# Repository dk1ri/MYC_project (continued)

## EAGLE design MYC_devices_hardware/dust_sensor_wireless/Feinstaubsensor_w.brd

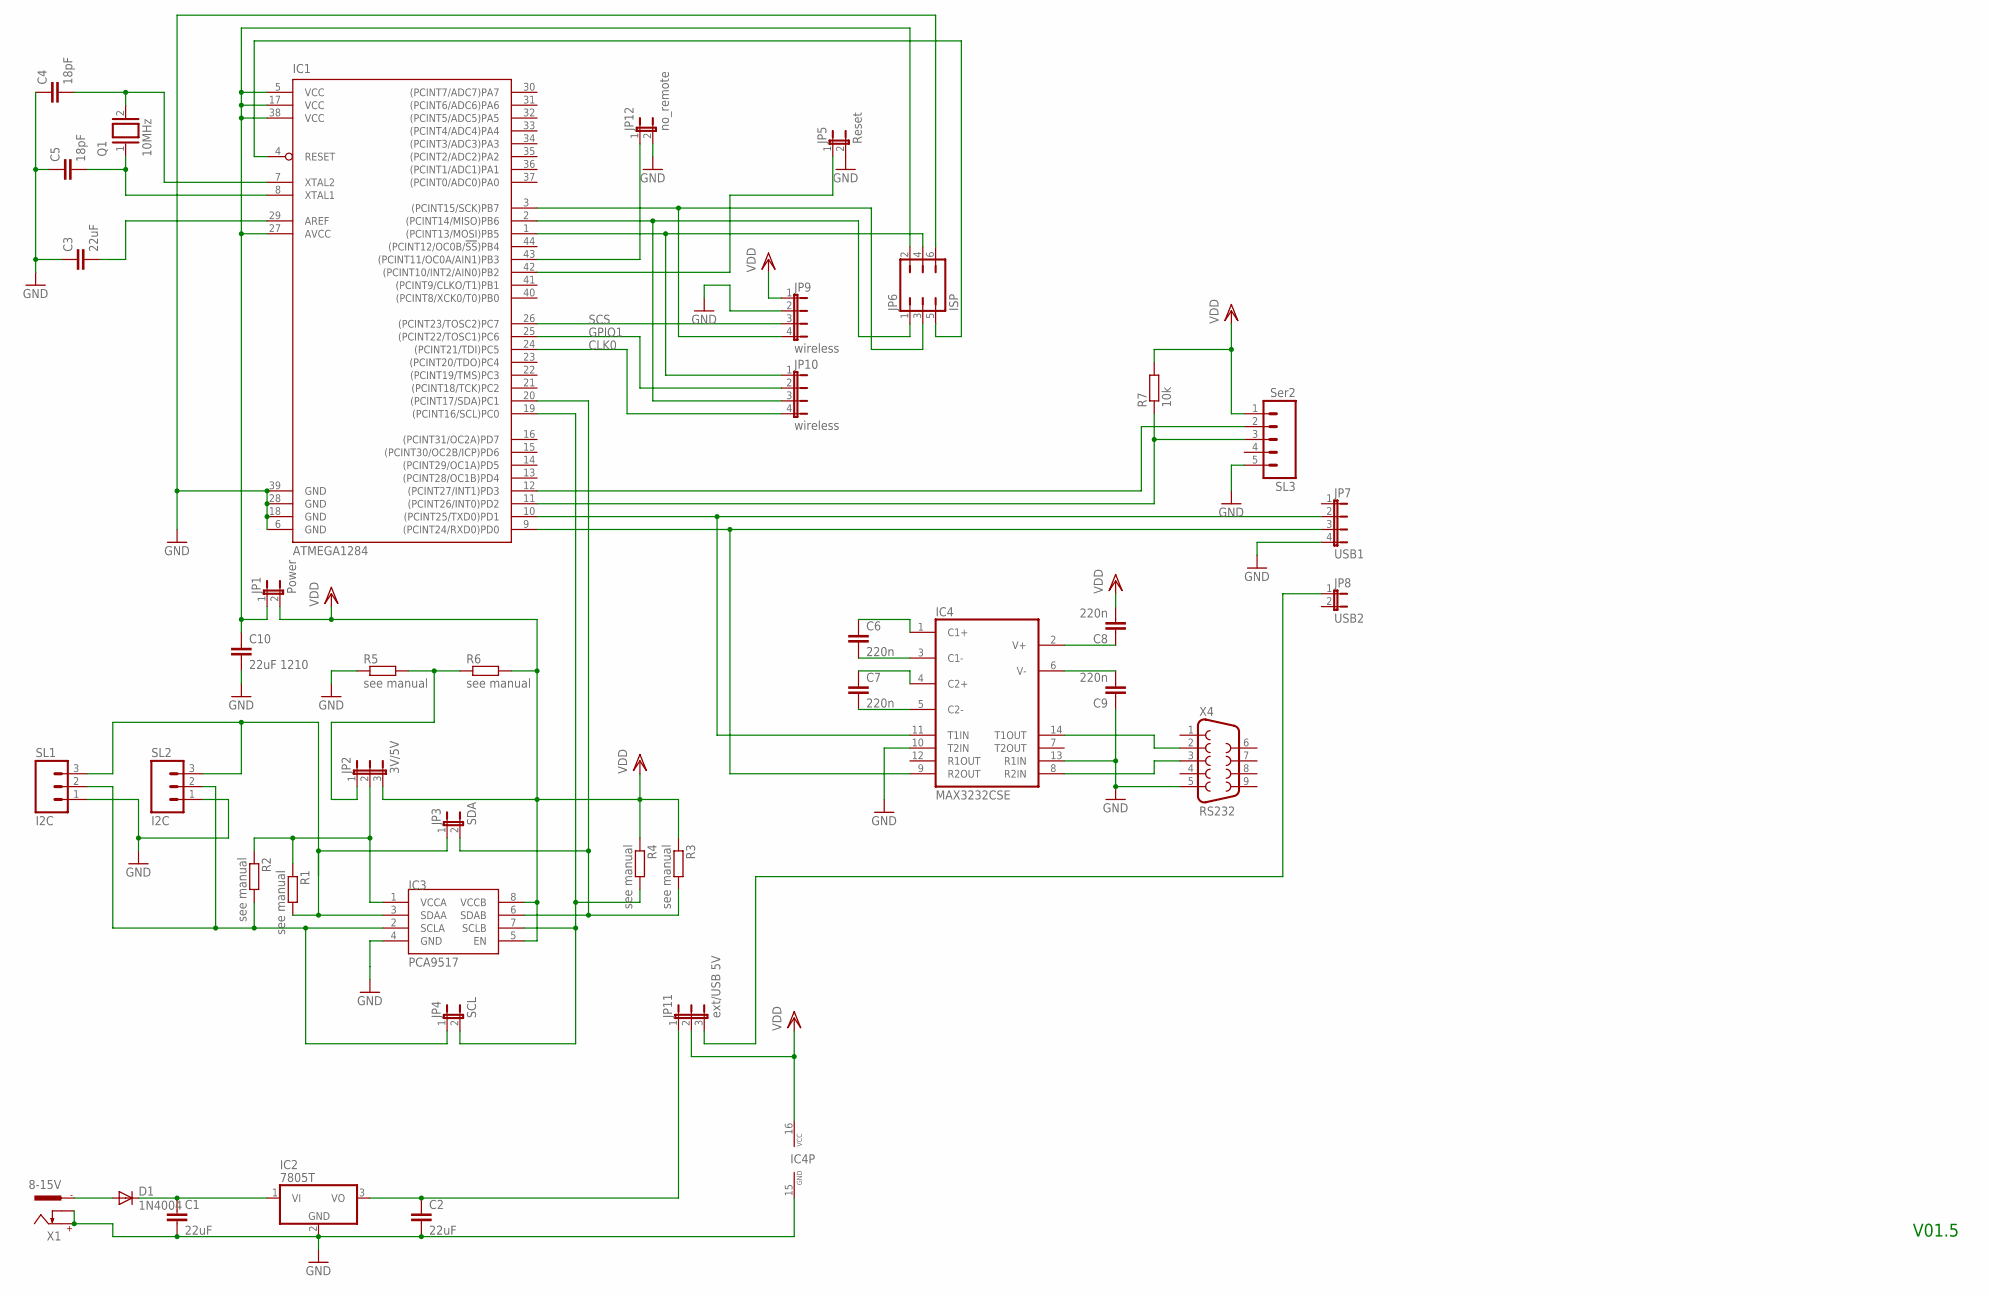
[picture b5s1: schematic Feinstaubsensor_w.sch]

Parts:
C1, C2, C3: 22uF; C1206
C4, C5: 18pF; C025-025X050
C6, C7, C8, C9: 220n; C1206
C10: 22uF 1210; C1206
D1: 1N4004; DO41-10
IC1: ATMEGA1284; TQFP44
IC2: 7805T; TO220H
IC3: PCA9517; SO-08
IC4: MAX3232CSE; SO16
JP1: Power; JP1
JP2: 3V/5V; JP2
JP3: SDA; JP1
JP4: SCL; JP1
JP5: Reset; JP1
JP6: ISP; JP3Q
JP7: USB1; JP4
JP8: USB2; JP1
JP9, JP10: wireless; JP4
JP11: ext/USB 5V; JP2
JP12: no_remote; JP1
Q1: 10MHz; QS
R1, R2, R3, R4, R5, R6: see manual; R1206
R7: 10k; R1206
SL1, SL2: I2C; 03P
SL3: Ser2; 05P
X1: 8-15V; 737992-5
X4: RS232; F09H

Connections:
C13: C6.1, IC4.1 (C1+)
CLK0: IC1.24 ((PCINT21/TDI)PC5), JP10.4
GND: C1.2, C2.2, C3.1, C4.1, C5.1, C9.1, C10.2, IC1.6 (GND), IC1.18 (GND), IC1.28 (GND), IC1.39 (GND), IC2.2 (GND), IC3.4 (GND), IC4.10 (T2IN), IC4.13 (R1IN), IC4.15 (GND), JP5.2, JP6.6, JP7.4, JP9.2, JP12.2, R5.1, SL1.1, SL2.1, SL3.5, X1.+, X1.K, X4.5
GPIO1: IC1.25 ((PCINT22/TOSC1)PC6), JP10.2
unnamed: IC1.9 ((PCINT24/RXD0)PD0), IC4.9 (R2OUT), JP7.3
unnamed: C7.2, IC4.5 (C2-)
unnamed: JP2.1, R5.2, R6.1
unnamed: IC1.20 ((PCINT17/SDA)PC1), IC3.6 (SDAB), JP3.2, R3.2
unnamed: C10.1, IC1.5 (VCC), IC1.17 (VCC), IC1.27 (AVCC), IC1.38 (VCC), JP1.1, JP6.2
unnamed: C4.2, IC1.7 (XTAL2), Q1.2
unnamed: IC1.1 ((PCINT13/MOSI)PB5), JP6.4, JP10.1
unnamed: IC4.14 (T1OUT), X4.2
unnamed: IC1.12 ((PCINT27/INT1)PD3), SL3.2
unnamed: IC1.10 ((PCINT25/TXD0)PD1), IC4.11 (T1IN), JP7.2
unnamed: C7.1, IC4.4 (C2+)
unnamed: C6.2, IC4.3 (C1-)
unnamed: IC1.42 ((PCINT10/INT2/AIN0)PB2), JP5.1
unnamed: C8.1, IC4.2 (V+)
unnamed: C9.2, IC4.6 (V-)
unnamed: IC1.4 (RESET), JP6.5
unnamed: IC1.11 ((PCINT26/INT0)PD2), R7.1, SL3.3
unnamed: IC1.43 ((PCINT11/OC0A/AIN1)PB3), JP12.1
unnamed: C5.2, IC1.8 (XTAL1), Q1.1
unnamed: IC1.19 ((PCINT16/SCL)PC0), IC3.7 (SCLB), JP4.2, R4.2
unnamed: IC3.3 (SDAA), JP3.1, R1.2, SL1.3, SL2.3
unnamed: C3.2, IC1.29 (AREF)
unnamed: IC3.2 (SCLA), JP4.1, R2.2, SL1.2, SL2.2
unnamed: IC1.3 ((PCINT15/SCK)PB7), JP6.3, JP9.4
unnamed: D1.A, X1.-1
unnamed: IC1.2 ((PCINT14/MISO)PB6), JP6.1, JP10.3
unnamed: C2.1, IC2.3 (VO), JP11.1
unnamed: IC3.1 (VCCA), JP2.2, R1.1, R2.1
unnamed: C1.1, D1.C, IC2.1 (VI)
unnamed: JP8.1, JP11.3
unnamed: IC4.8 (R2IN), X4.3
SCS: IC1.26 ((PCINT23/TOSC2)PC7), JP9.3
VDD: C8.2, IC3.5 (EN), IC3.8 (VCCB), IC4.16 (VCC), JP1.2, JP2.3, JP9.1, JP11.2, R3.1, R4.1, R6.2, R7.2, SL3.1

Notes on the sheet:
V01.5

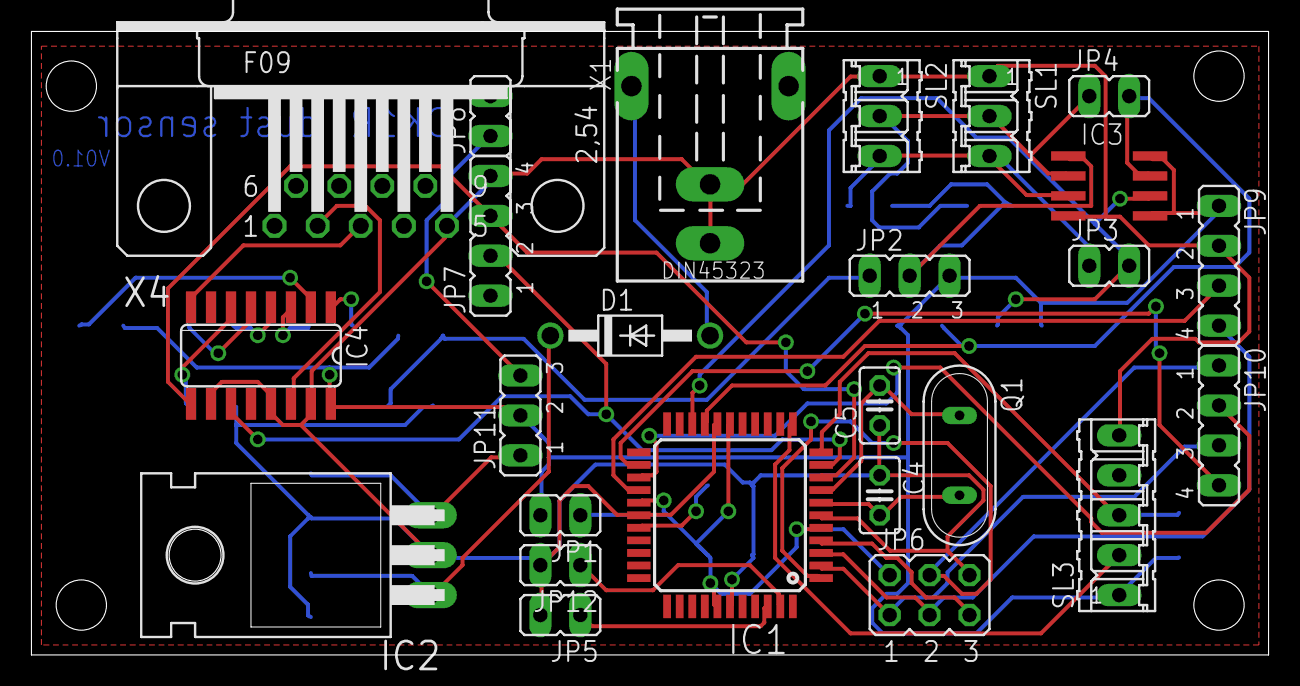
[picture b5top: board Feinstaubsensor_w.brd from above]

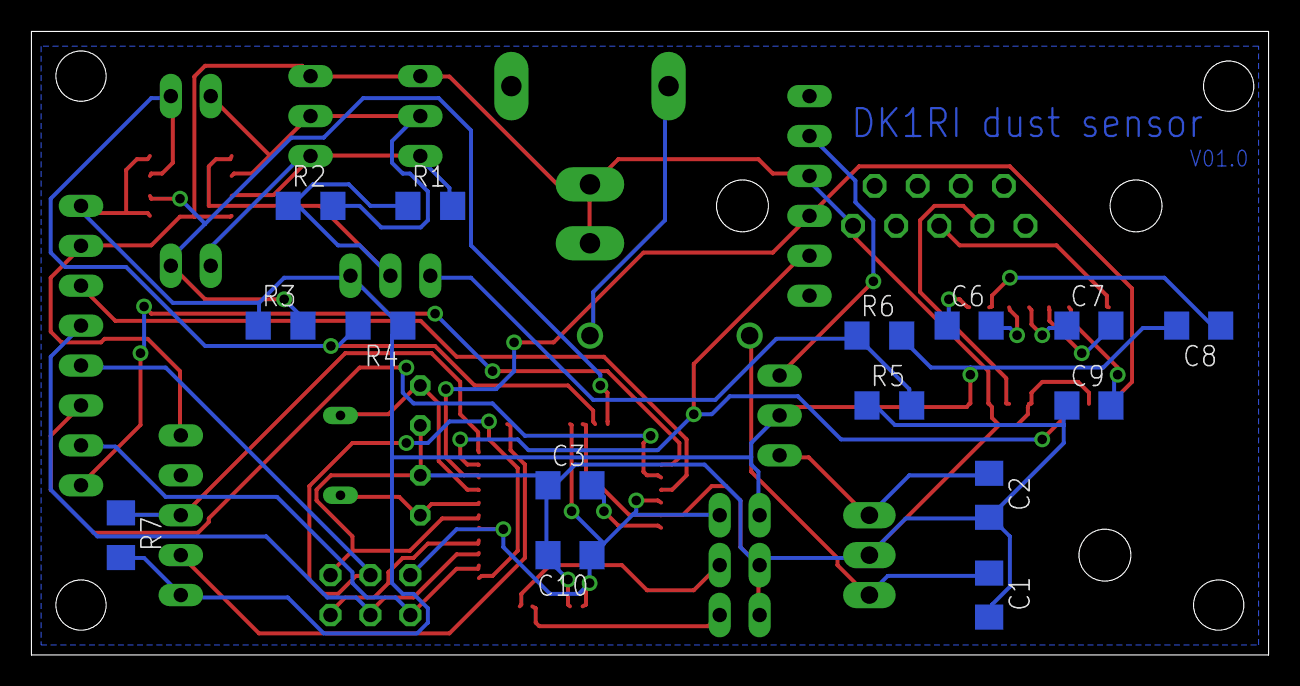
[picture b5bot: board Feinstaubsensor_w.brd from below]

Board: 2 copper layers, 78.7 x 39.7 mm, 40 parts (15 on the bottom side), 37 nets.

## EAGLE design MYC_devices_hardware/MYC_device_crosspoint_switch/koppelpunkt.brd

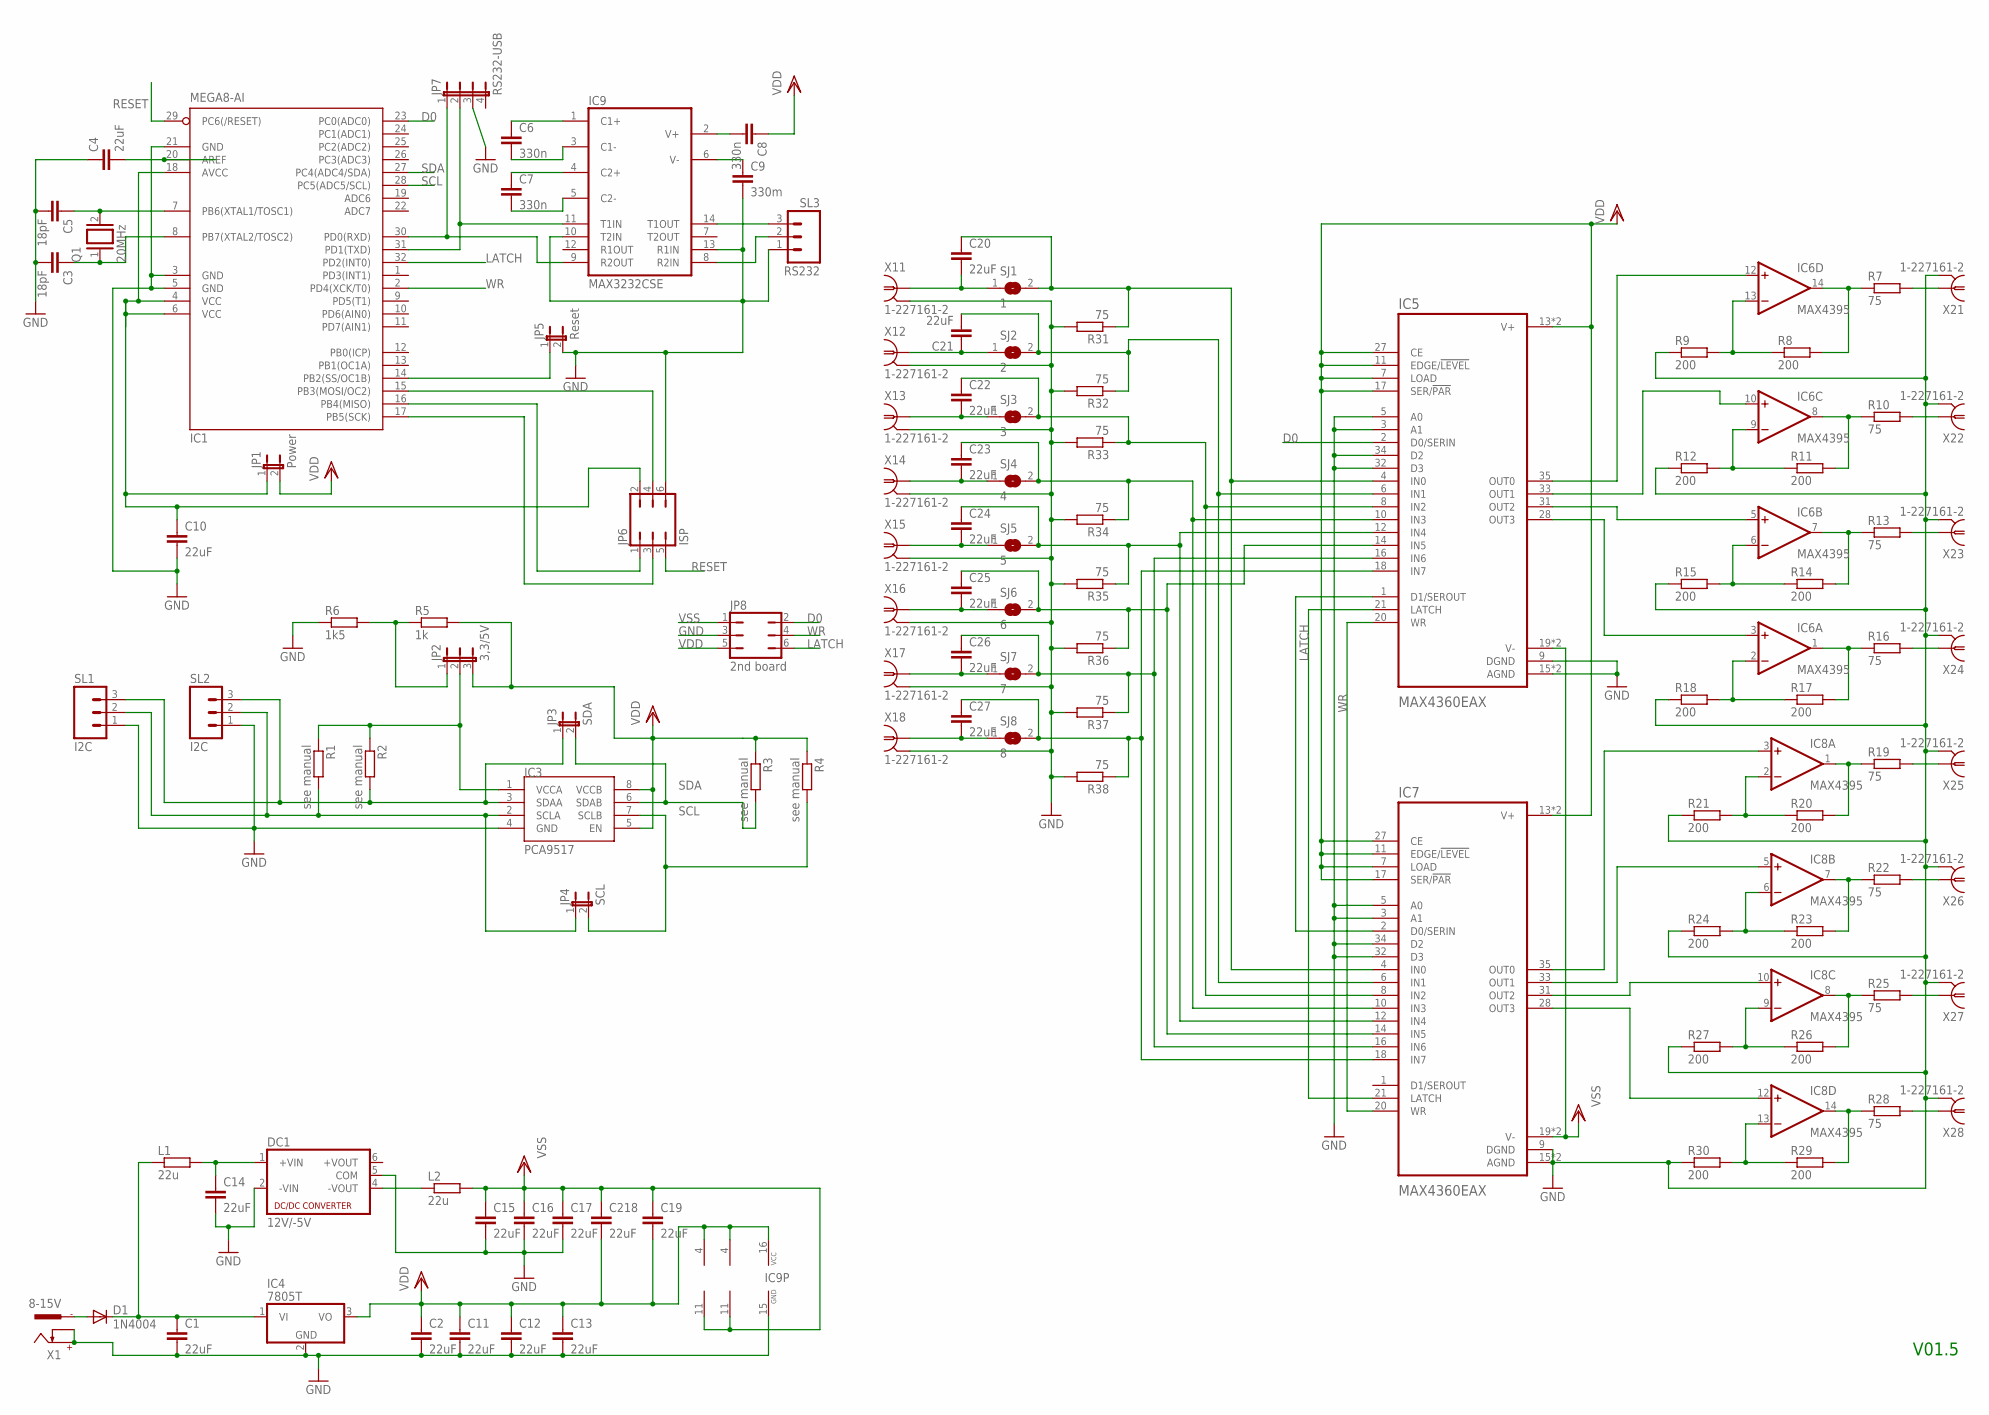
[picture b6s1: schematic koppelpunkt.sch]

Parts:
C1, C2, C4, C10, C11, C12, C13, C14, C15, C16, C17, C19, C20, C21, C22, C23, C24, C25, C26, C27, C218: 22uF; C1206
C3, C5: 18pF; C025-025X050
C6, C7, C8: 330n; C1206
C9: 330m; C1206
D1: 1N4004; DO41-10
DC1: 12V/-5V; NMA
IC1: MEGA8-AI; TQFP32-08
IC3: PCA9517; SO-08
IC4: 7805T; TO220H
IC5, IC7: MAX4360EAX; SOP80P1030X264-36N
IC6, IC8: MAX4395; SO14
IC9: MAX3232CSE; SO16
JP1: Power; JP1
JP2: 3,3/5V; JP2
JP3: SDA; JP1
JP4: SCL; JP1
JP5: Reset; JP1
JP6: ISP; JP3Q
JP7: RS232-USB; JP4
JP8: 2nd board; JP3Q
L1, L2: 22u; R6332
Q1: 20MHz; QS
R1, R2, R3, R4: see manual; R1206
R5: 1k; R1206
R6: 1k5; R1206
R7, R10, R13, R16, R19, R22, R25, R28, R31, R32, R33, R34, R35, R36, R37, R38: 75; R1206
R8, R11, R12, R14, R15, R17, R18, R20, R21, R23, R24, R26, R27, R29, R30: 200; R1206
R9: 200; M1206
SJ1: 1; SJ
SJ2: 2; SJ
SJ3: 3; SJ
SJ4: 4; SJ
SJ5: 5; SJ
SJ6: 6; SJ
SJ7: 7; SJ
SJ8: 8; SJ
SL1, SL2: I2C; 03P
SL3: RS232; 03P
X1: 8-15V; 737992-5
X11, X12, X13, X14, X15, X16, X17, X18, X21, X22, X23, X24, X25, X26, X27, X28: 1-227161-2; AMP_227161

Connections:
D0: IC1.23 (PC0(ADC0)), IC5.2 (D0/SERIN), JP8.2
GND: C1.2, C2.2, C3.2, C4.1, C5.2, C9.2, C10.2, C11.2, C12.2, C13.2, C14.2, C15.2, C16.2, C17.2, DC1.2 (-VIN), DC1.5 (COM), IC1.3 (GND), IC1.5 (GND), IC1.21 (GND), IC3.4 (GND), IC4.2 (GND), IC5.3 (A1), IC5.5 (A0), IC5.9 (DGND), IC5.15 (AGND), IC5.29 (AGND), IC5.32 (D3), IC5.34 (D2), IC7.3 (A1), IC7.5 (A0), IC7.9 (DGND), IC7.15 (AGND), IC7.29 (AGND), IC7.32 (D3), IC7.34 (D2), IC9.10 (T2IN), IC9.13 (R1IN), IC9.15 (GND), JP5.2, JP6.6, JP7.3, JP8.3, R6.1, R9.1, R12.1, R15.1, R18.1, R21.1, R24.1, R27.1, R30.1, R31.2, R32.2, R33.2, R34.2, R35.2, R36.2, R37.2, R38.2, SL1.1, SL2.1, SL3.1, X1.+, X1.K, X11.2, X12.2, X13.2, X14.2, X15.2, X16.2, X17.2, X18.2, X21.2, X22.2, X23.2, X24.2, X25.2, X26.2, X27.2, X28.2
LATCH: IC1.32 (PD2(INT0)), IC5.21 (LATCH), IC7.21 (LATCH), JP8.6
unnamed: C23.1, IC5.10 (IN3), IC7.10 (IN3), R34.1, SJ4.2
unnamed: C5.1, IC1.7 (PB6(XTAL1/TOSC1)), Q1.2
unnamed: C3.1, IC1.8 (PB7(XTAL2/TOSC2)), Q1.1
unnamed: C4.2, IC1.20 (AREF)
unnamed: IC3.3 (SDAA), JP3.1, R2.2, SL1.3, SL2.3
unnamed: IC1.16 (PB4(MISO)), JP6.1
unnamed: D1.A, X1.-1
unnamed: C10.1, IC1.4 (VCC), IC1.6 (VCC), IC1.18 (AVCC), JP1.1, JP6.2
unnamed: IC1.17 (PB5(SCK)), JP6.3
unnamed: IC1.14 (PB2(SS/OC1B)), JP5.1
unnamed: IC1.15 (PB3(MOSI/OC2)), JP6.4
unnamed: C7.2, IC9.5 (C2-)
unnamed: IC3.1 (VCCA), JP2.2, R1.1, R2.1
unnamed: IC3.2 (SCLA), JP4.1, R1.2, SL1.2, SL2.2
unnamed: IC9.14 (T1OUT), SL3.3
unnamed: C8.2, IC9.2 (V+)
unnamed: C22.1, IC5.8 (IN2), IC7.8 (IN2), R33.1, SJ3.2
unnamed: R7.2, X21.1
unnamed: IC6.14 (OUT), R7.1, R8.2
unnamed: IC9.8 (R2IN), SL3.2
unnamed: IC6.13 (-IN), R8.1, R9.2
unnamed: C7.1, IC9.4 (C2+)
unnamed: R10.2, X22.1
unnamed: JP2.1, R5.1, R6.2
unnamed: IC6.8 (OUT), R10.1, R11.2
unnamed: IC6.9 (-IN), R11.1, R12.2
unnamed: R13.2, X23.1
unnamed: C9.1, IC9.6 (V-)
unnamed: IC5.1 (D1/SEROUT), IC7.2 (D0/SERIN)
unnamed: IC6.7 (OUT), R13.1, R14.2
unnamed: IC6.6 (-IN), R14.1, R15.2
unnamed: C1.1, D1.C, IC4.1 (VI), L1.1
unnamed: IC1.30 (PD0(RXD)), IC9.9 (R2OUT), JP7.1
unnamed: R22.2, X26.1
unnamed: IC8.7 (OUT), R22.1, R23.2
unnamed: IC8.6 (-IN), R23.1, R24.2
unnamed: IC6.1 (OUT), R16.1, R17.2
unnamed: R16.2, X24.1
unnamed: IC6.2 (-IN), R17.1, R18.2
unnamed: IC8.9 (-IN), R26.1, R27.2
unnamed: IC8.2 (-IN), R20.1, R21.2
unnamed: IC8.1 (OUT), R19.1, R20.2
unnamed: IC1.31 (PD1(TXD)), IC9.11 (T1IN), JP7.2
unnamed: R19.2, X25.1
unnamed: R25.2, X27.1
unnamed: IC8.8 (OUT), R25.1, R26.2
unnamed: C6.1, IC9.1 (C1+)
unnamed: R28.2, X28.1
unnamed: IC8.14 (OUT), R28.1, R29.2
unnamed: IC8.13 (-IN), R29.1, R30.2
unnamed: C6.2, IC9.3 (C1-)
unnamed: IC5.35 (OUT0), IC6.12 (+IN)
unnamed: IC5.33 (OUT1), IC6.10 (+IN)
unnamed: IC5.31 (OUT2), IC6.5 (+IN)
unnamed: IC5.28 (OUT3), IC6.3 (+IN)
unnamed: C14.1, DC1.1 (+VIN), L1.2
unnamed: IC7.35 (OUT0), IC8.3 (+IN)
unnamed: C20.2, SJ1.1, X11.1
unnamed: C26.1, IC5.16 (IN6), IC7.16 (IN6), R37.1, SJ7.2
unnamed: IC7.33 (OUT1), IC8.5 (+IN)
unnamed: IC7.31 (OUT2), IC8.10 (+IN)
unnamed: IC7.28 (OUT3), IC8.12 (+IN)
unnamed: C21.1, SJ2.1, X12.1
unnamed: C22.2, SJ3.1, X13.1
unnamed: C20.1, IC5.4 (IN0), IC7.4 (IN0), R31.1, SJ1.2
unnamed: C21.2, IC5.6 (IN1), IC7.6 (IN1), R32.1, SJ2.2
unnamed: C23.2, SJ4.1, X14.1
unnamed: C24.2, SJ5.1, X15.1
unnamed: C24.1, IC5.12 (IN4), IC7.12 (IN4), R35.1, SJ5.2
unnamed: C25.2, SJ6.1, X16.1
unnamed: C26.2, SJ7.1, X17.1
unnamed: C27.2, SJ8.1, X18.1
unnamed: C27.1, IC5.18 (IN7), IC7.18 (IN7), R38.1, SJ8.2
unnamed: DC1.4 (-VOUT), L2.1
unnamed: C25.1, IC5.14 (IN5), IC7.14 (IN5), R36.1, SJ6.2
RESET: IC1.29 (PC6(/RESET)), JP6.5
SCL: IC1.28 (PC5(ADC5/SCL)), IC3.7 (SCLB), JP4.2, R4.2
SDA: IC1.27 (PC4(ADC4/SDA)), IC3.6 (SDAB), JP3.2, R3.2
VDD: C2.1, C8.1, C11.1, C12.1, C13.1, C19.2, C218.2, IC3.5 (EN), IC3.8 (VCCB), IC4.3 (VO), IC5.7 (LOAD), IC5.11 (EDGE/!LEVEL), IC5.13 (V+), IC5.17 (SER/!PAR), IC5.27 (CE), IC5.36 (V+), IC6.4 (V+), IC7.7 (LOAD), IC7.11 (EDGE/!LEVEL), IC7.13 (V+), IC7.17 (SER/!PAR), IC7.27 (CE), IC7.36 (V+), IC8.4 (V+), IC9.16 (VCC), JP1.2, JP2.3, JP8.5, R3.1, R4.1, R5.2
VSS: C15.1, C16.1, C17.1, C19.1, C218.1, IC5.19 (V-), IC5.30 (V-), IC6.11 (V-), IC7.19 (V-), IC7.30 (V-), IC8.11 (V-), JP8.1, L2.2
WR: IC1.2 (PD4(XCK/T0)), IC5.20 (WR), IC7.20 (WR), JP8.4

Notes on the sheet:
V01.5

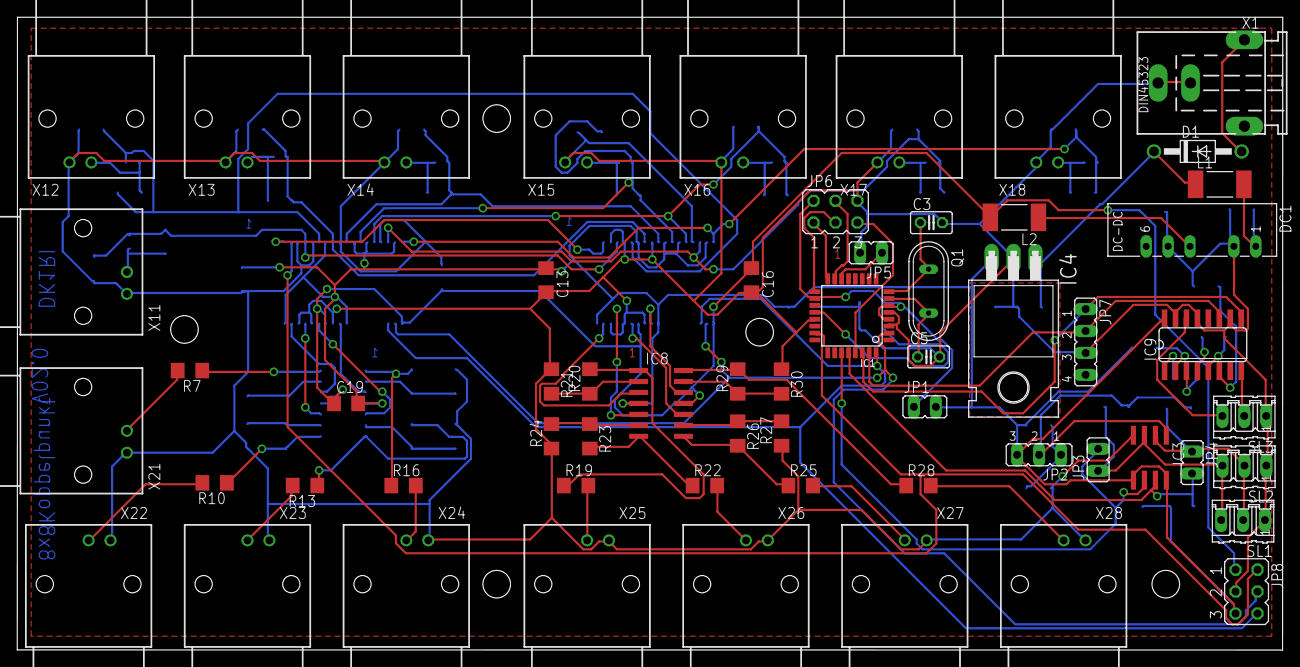
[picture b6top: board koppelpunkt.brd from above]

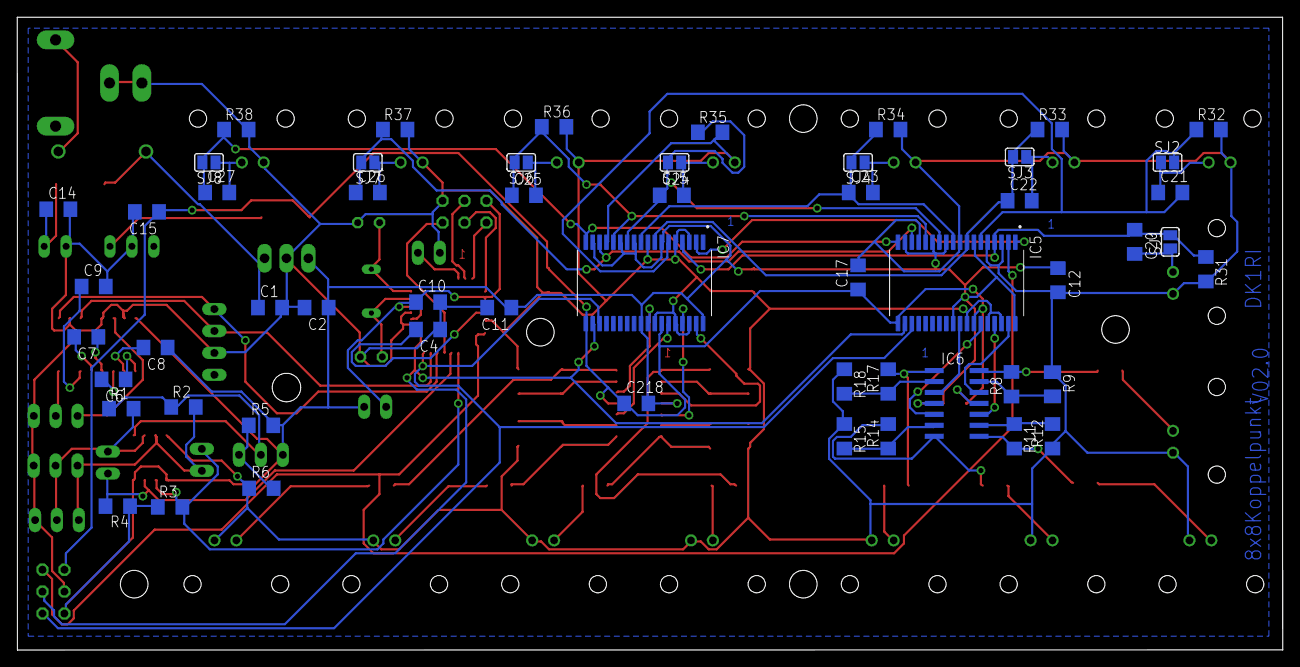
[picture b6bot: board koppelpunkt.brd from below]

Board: 3 copper layers, 146.7 x 73.4 mm, 114 parts (55 on the bottom side), 84 nets.

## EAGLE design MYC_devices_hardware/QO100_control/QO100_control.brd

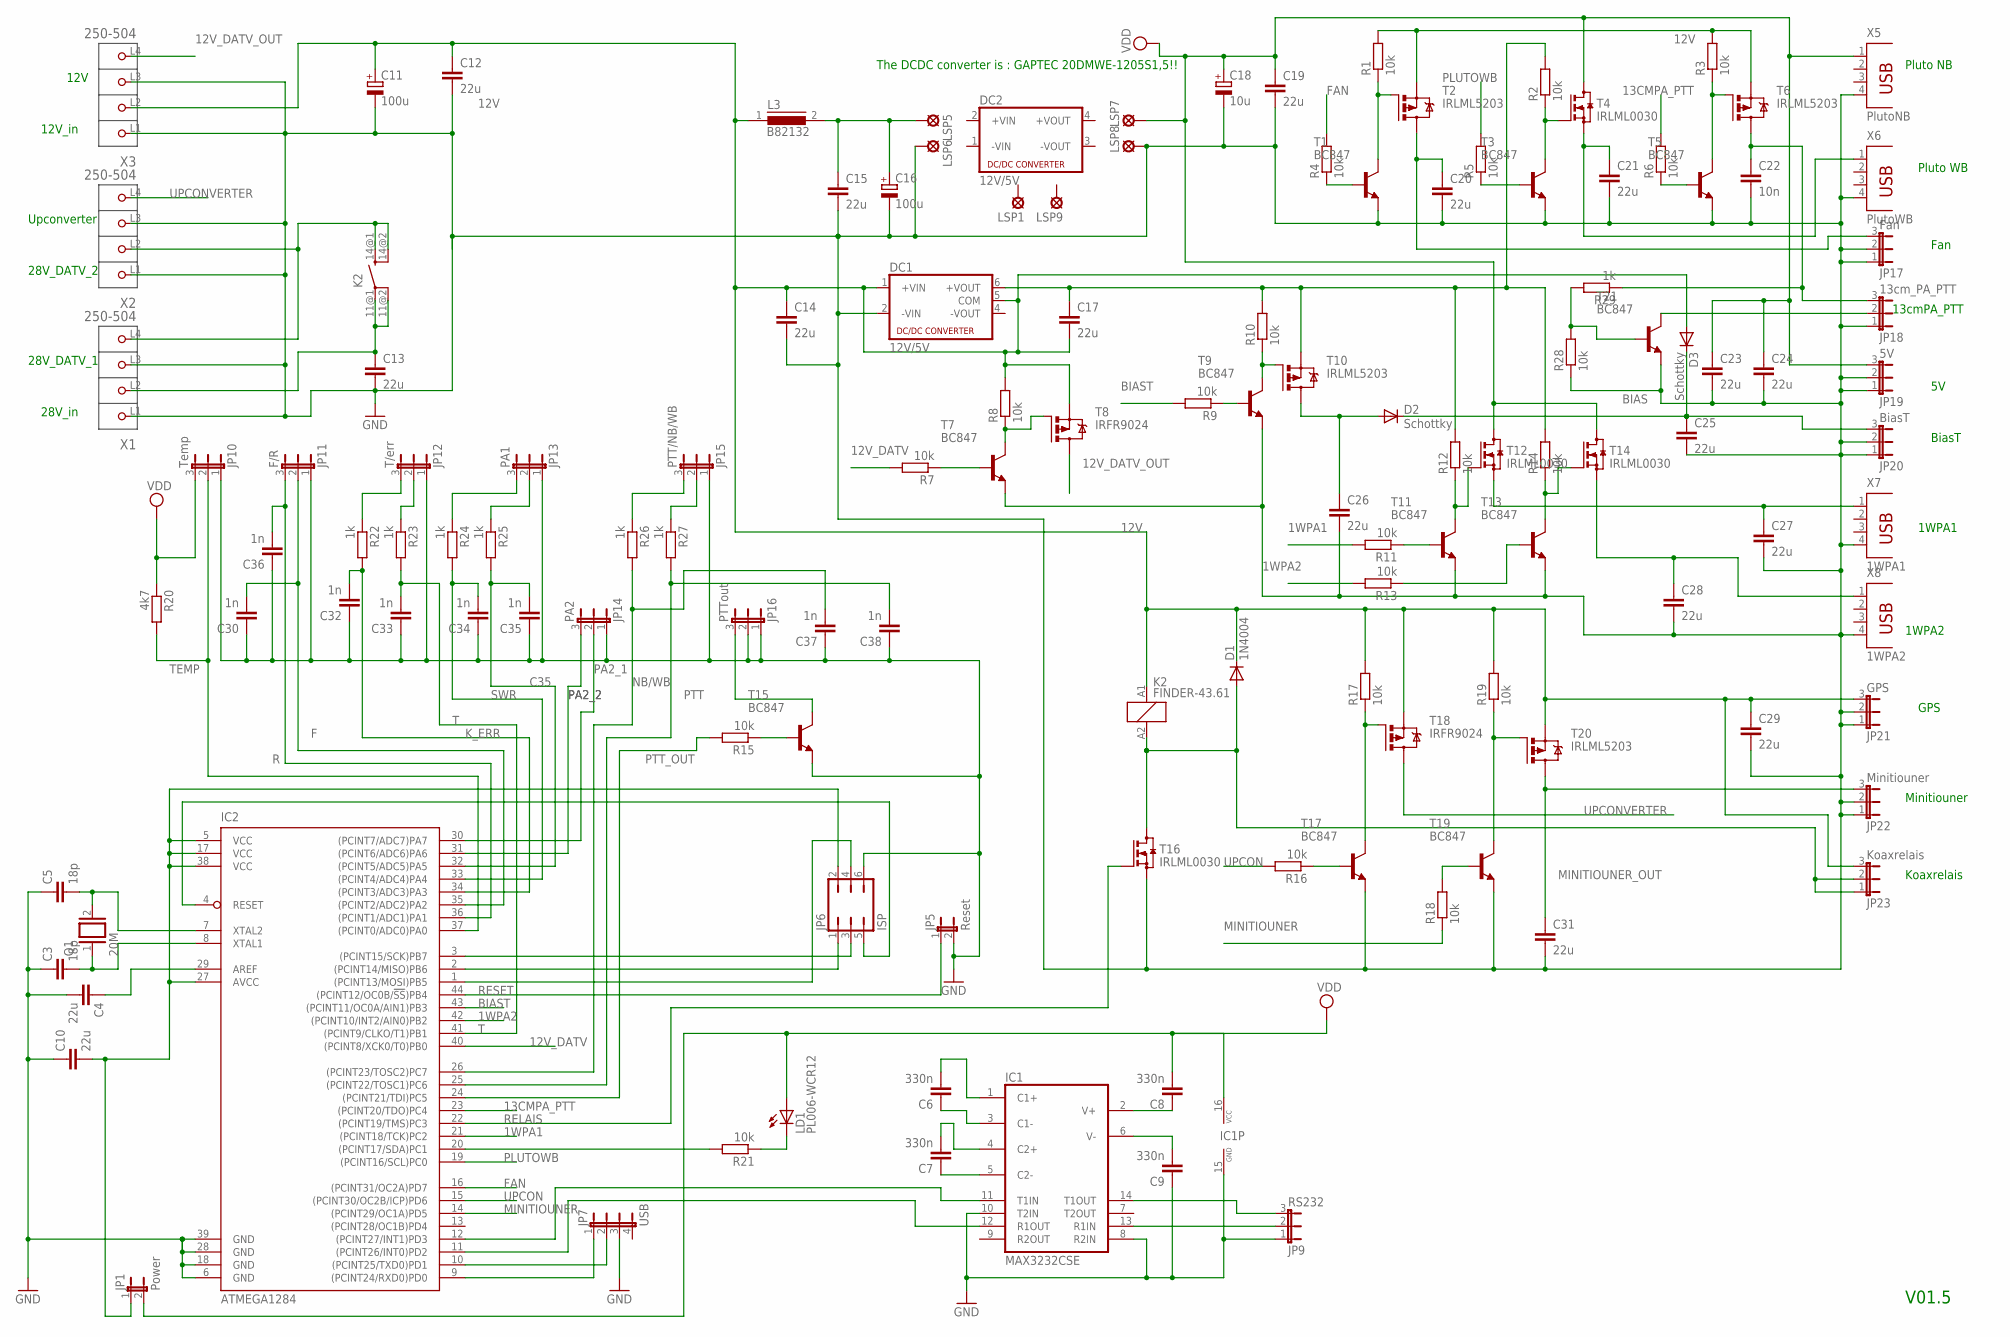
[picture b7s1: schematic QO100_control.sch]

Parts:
C3, C5: 18p; C025-025X050
C4, C10, C12, C13, C14, C15, C17, C19, C20, C21, C23, C24, C25, C26, C27, C28, C29, C31: 22u; C1206
C6, C7, C8, C9: 330n; C1206
C11, C16: 100u; E5-6
C18: 10u; E5-6
C22: 10n; C1206
C30, C32, C33, C34, C35, C36, C37, C38: 1n; C1206
D1: 1N4004; DO41-10
D2, D3: Schottky; DO41-10
DC1: 12V/5V; NMA
DC2: 12V/5V; NME
IC1: MAX3232CSE; SO16
IC2: ATMEGA1284; TQFP44
JP1: Power; JP1
JP5: Reset; JP1
JP6: ISP; JP3Q
JP7: USB; JP4
JP9: RS232; JP2
JP10: Temp; JP2
JP11: F/R; JP2
JP12: T/err; JP2
JP13: PA1; JP2
JP14: PA2; JP2
JP15: PTT/NB/WB; JP2
JP16: PTTout; JP2
JP17: Fan; JP2
JP18: 13cm_PA_PTT; JP2
JP19: 5V; JP2
JP20: BiasT; JP2
JP21: GPS; JP2
JP22: Minitiouner; JP2
JP23: Koaxrelais; JP2
K2: FINDER-43.61
L3: B82132; SUKW2-22
LD1: PL006-WCR12; SOT23
LSP1, LSP5, LSP6, LSP7, LSP8, LSP9: SE14
Q1: 20M; QS
R1, R2, R3, R4, R5, R6, R7, R8, R9, R10, R11, R12, R13, R14, R15, R16, R17, R18, R19, R21, R28: 10k; R1206
R20: 4k7; R1206
R22, R23, R24, R25, R26, R27, R29: 1k; R1206
T1, T3, T5, T7, T9, T11, T13, T15, T17, T19, T21: BC847; SOT23
T2, T6, T10, T20: IRLML5203; MICRO3
T4, T12, T14, T16: IRLML0030; SOT23
T8, T18: IRFR9024; D-PAK_TO252AA
X1, X2, X3: 250-504; P-250-504
X5: PlutoNB; PN87520
X6: PlutoWB; PN87520
X7: 1WPA1; PN87520
X8: 1WPA2; PN87520

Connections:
1WPA1: IC2.21 ((PCINT18/TCK)PC2), R11.2
1WPA2: IC2.42 ((PCINT10/INT2/AIN0)PB2), R13.2
12V: C11.+, C12.1, C14.1, C17.2, C29.1, D1.C, D3.A, DC1.1 (+VIN), DC1.5 (COM), JP21.3, JP23.3, K2.A1 (1), L3.1, R1.2, R3.2, R8.2, R17.2, R19.2, T2.2 (S), T6.2 (S), T8.3 (S), T18.3 (S), T20.2 (S), X3.L2 (P2)
12V_DATV: IC2.40 ((PCINT8/XCK0/T0)PB0), R7.2
12V_DATV_OUT: T8.4 (D), X3.L4 (P4)
13CMPA_PTT: IC2.23 ((PCINT20/TDO)PC4), R6.2
28V: K2.14@1 (SA), K2.14@2 (SB), X1.L4 (P4), X2.L2 (P2)
BIAS: C25.1, D2.C, D3.C, JP20.3
BIAST: IC2.43 ((PCINT11/OC0A/AIN1)PB3), R9.2
C35: C35.2, IC2.32 ((PCINT5/ADC5)PA5), R25.2
DFGJKN: C26.1, D2.A, T10.3 (D)
F: C30.2, IC2.35 ((PCINT2/ADC2)PA2), JP11.2
FAN: IC2.16 ((PCINT31/OC2A)PD7), R4.2
GND: C3.1, C4.2, C5.1, C9.1, C10.1, C11.-, C12.2, C13.2, C14.2, C15.2, C16.-, C18.-, C19.2, C20.2, C21.2, C22.2, C23.2, C24.2, C25.2, C26.2, C27.2, C28.2, C29.2, C30.1, C31.2, C32.1, C33.1, C34.1, C35.1, C36.1, C37.1, C38.1, DC1.2 (-VIN), IC1.8 (R2IN), IC1.10 (T2IN), IC1.15 (GND), IC2.6 (GND), IC2.18 (GND), IC2.28 (GND), IC2.39 (GND), JP5.2, JP6.6, JP7.3, JP9.1, JP10.1, JP11.1, JP12.1, JP13.1, JP14.1, JP15.1, JP16.1, JP16.2, JP17.1, JP17.2, JP18.1, JP19.1, JP19.2, JP20.1, JP20.2, JP21.1, JP21.2, JP22.1, JP22.2, LSP6.MP, LSP8.MP, R28.1, T1.2 (E), T3.2 (E), T5.2 (E), T7.2 (E), T9.2 (E), T11.2 (E), T13.2 (E), T15.2 (E), T16.2 (S), T17.2 (E), T19.2 (E), T21.2 (E), X1.L1 (P1), X1.L3 (P3), X2.L1 (P1), X2.L3 (P3), X3.L1 (P1), X3.L3 (P3), X5.4, X6.4, X7.4, X8.4
K_ERR: C32.2, IC2.34 ((PCINT3/ADC3)PA3), R22.2
MINITIOUNER: IC2.14 ((PCINT29/OC1A)PD5), R18.1
MINITIOUNER_OUT: C31.1, JP22.3, T20.3 (D)
unnamed: IC2.20 ((PCINT17/SDA)PC1), R21.2
unnamed: C22.1, JP18.3, R29.1, T6.3 (D)
unnamed: C28.1, T14.2 (S), X8.1
unnamed: IC2.3 ((PCINT15/SCK)PB7), JP6.3
unnamed: R17.1, T17.3 (C), T18.1 (G)
unnamed: C5.2, IC2.7 (XTAL2), Q1.2
unnamed: C15.1, C16.+, L3.2, LSP5.MP
unnamed: R8.1, T7.3 (C), T8.1 (G)
unnamed: LD1.3 (C), R21.1
unnamed: C3.2, IC2.8 (XTAL1), Q1.1
unnamed: R7.1, T7.1 (B)
unnamed: JP12.3, R22.1
unnamed: IC2.2 ((PCINT14/MISO)PB6), JP6.1
unnamed: C6.2, IC1.1 (C1+)
unnamed: IC2.1 ((PCINT13/MOSI)PB5), JP6.4
unnamed: IC2.4 (RESET), JP6.5
unnamed: IC2.9 ((PCINT24/RXD0)PD0), JP7.1
unnamed: IC2.10 ((PCINT25/TXD0)PD1), JP7.2
unnamed: IC1.12 (R1OUT), IC2.11 ((PCINT26/INT0)PD2)
unnamed: C4.1, IC2.29 (AREF)
unnamed: IC1.11 (T1IN), IC2.12 ((PCINT27/INT1)PD3)
unnamed: JP12.2, R23.1
unnamed: JP13.2, R25.1
unnamed: JP13.3, R24.1
unnamed: JP15.3, R26.1
unnamed: C27.1, T12.2 (S), X7.1
unnamed: JP15.2, R27.1
unnamed: D1.A, JP23.1, JP23.2, K2.A2 (2), T16.3 (D)
unnamed: C6.1, IC1.3 (C1-)
unnamed: C7.1, IC1.5 (C2-)
unnamed: C7.2, IC1.4 (C2+)
unnamed: JP18.2, T21.3 (C)
unnamed: IC1.14 (T1OUT), JP9.3
unnamed: C9.2, IC1.6 (V-)
unnamed: C8.1, IC1.2 (V+)
unnamed: IC1.13 (R1IN), JP9.2
unnamed: R28.2, R29.2, T21.1 (B)
unnamed: R3.1, T5.3 (C), T6.1 (G)
unnamed: JP16.3, T15.3 (C)
unnamed: C21.1, T4.2 (S), X6.1
unnamed: R15.1, T15.1 (B)
unnamed: R19.1, T19.3 (C), T20.1 (G)
unnamed: R10.1, T9.3 (C), T10.1 (G)
unnamed: R6.1, T5.1 (B)
unnamed: C20.1, JP17.3, T2.3 (D)
unnamed: R2.1, T3.3 (C), T4.1 (G)
unnamed: R12.1, T11.3 (C), T12.1 (G)
unnamed: R1.1, T1.3 (C), T2.1 (G)
unnamed: C17.1, DC1.6 (+VOUT), R2.2, R10.2, R12.2, R14.2, T10.2 (S)
unnamed: R14.1, T13.3 (C), T14.1 (G)
unnamed: R4.1, T1.1 (B)
unnamed: R5.1, T3.1 (B)
unnamed: R9.1, T9.1 (B)
unnamed: R11.1, T11.1 (B)
unnamed: R13.1, T13.1 (B)
unnamed: R16.1, T17.1 (B)
unnamed: C13.1, K2.11@1 (PA), K2.11@2 (PB), X1.L2 (P2)
unnamed: R18.2, T19.1 (B)
NB/WB: C37.2, IC2.26 ((PCINT23/TOSC2)PC7), R26.2
PA2_1: IC2.30 ((PCINT7/ADC7)PA7), JP14.2
PA2_2: IC2.31 ((PCINT6/ADC6)PA6), JP14.3
PLUTOWB: IC2.19 ((PCINT16/SCL)PC0), R5.2
PTT: C38.2, IC2.25 ((PCINT22/TOSC1)PC6), R27.2
PTT_OUT: IC2.24 ((PCINT21/TDI)PC5), R15.2
R: C36.2, IC2.36 ((PCINT1/ADC1)PA1), JP11.3
RELAIS: IC2.22 ((PCINT19/TMS)PC3), T16.1 (G)
RESET: IC2.44 ((PCINT12/OC0B/!SS!)PB4), JP5.1
SWR: C34.2, IC2.33 ((PCINT4/ADC4)PA4), R24.2
T: C33.2, IC2.41 ((PCINT9/CLKO/T1)PB1), R23.2
TEMP: IC2.37 ((PCINT0/ADC0)PA0), JP10.2, R20.2
UPCON: IC2.15 ((PCINT30/OC2B/ICP)PD6), R16.2
UPCONVERTER: T18.4 (D), X2.L4 (P4)
VCC: C10.2, IC2.5 (VCC), IC2.17 (VCC), IC2.27 (AVCC), IC2.38 (VCC), JP1.1, JP6.2
VDD: C8.2, C18.+, C19.1, C23.1, C24.1, IC1.16 (VCC), JP1.2, JP10.3, JP19.3, LD1.1 (A), LSP7.MP, R20.1, T4.3 (D), T12.3 (D), T14.3 (D), X5.1

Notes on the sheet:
V01.5
28V_in
BiasT
1WPA2
Koaxrelais
Upconverter
GPS
The DCDC converter is : GAPTEC 20DMWE-1205S1,5!!
Pluto NB
Pluto WB
Fan
13cmPA_PTT
12V_in
12V
28V_DATV_1
28V_DATV_2
1WPA1
Minitiouner

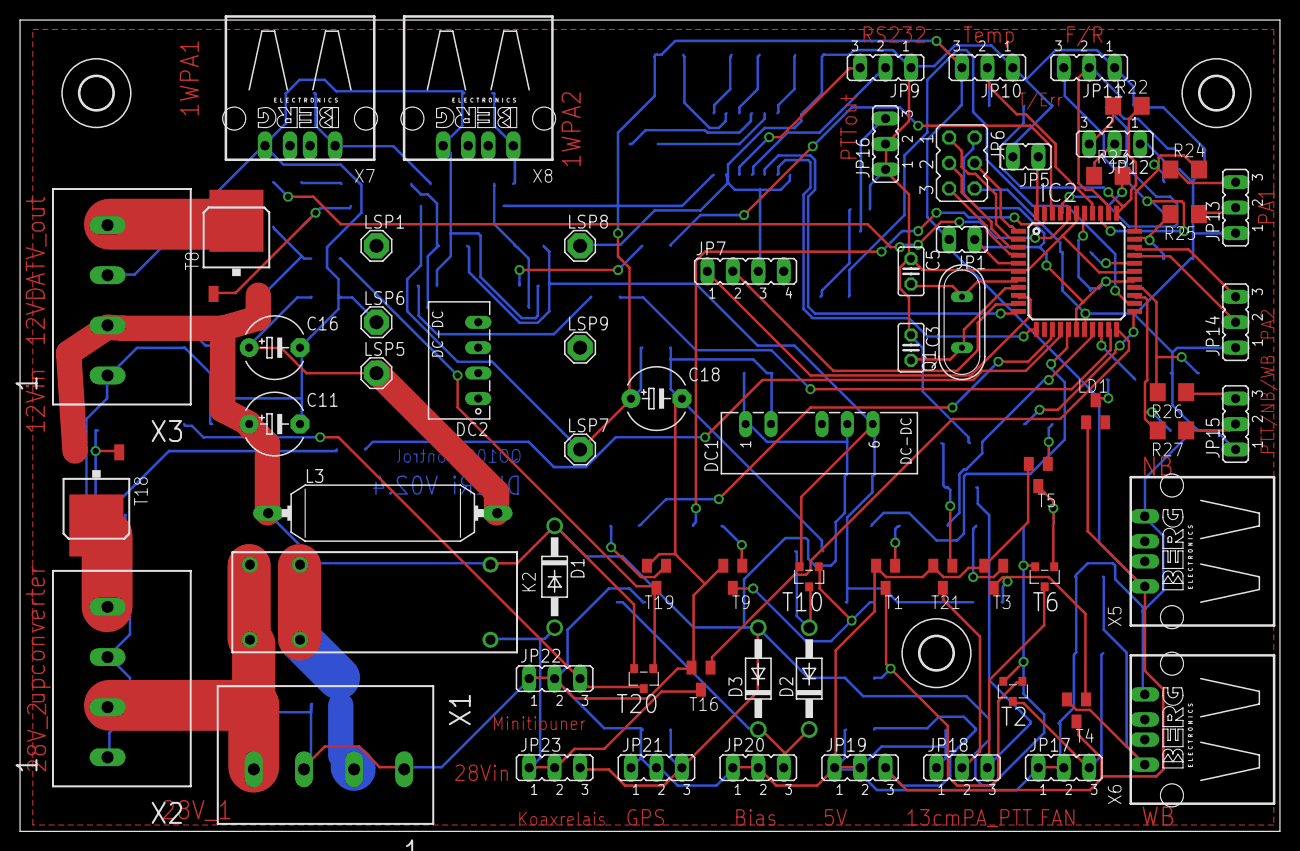
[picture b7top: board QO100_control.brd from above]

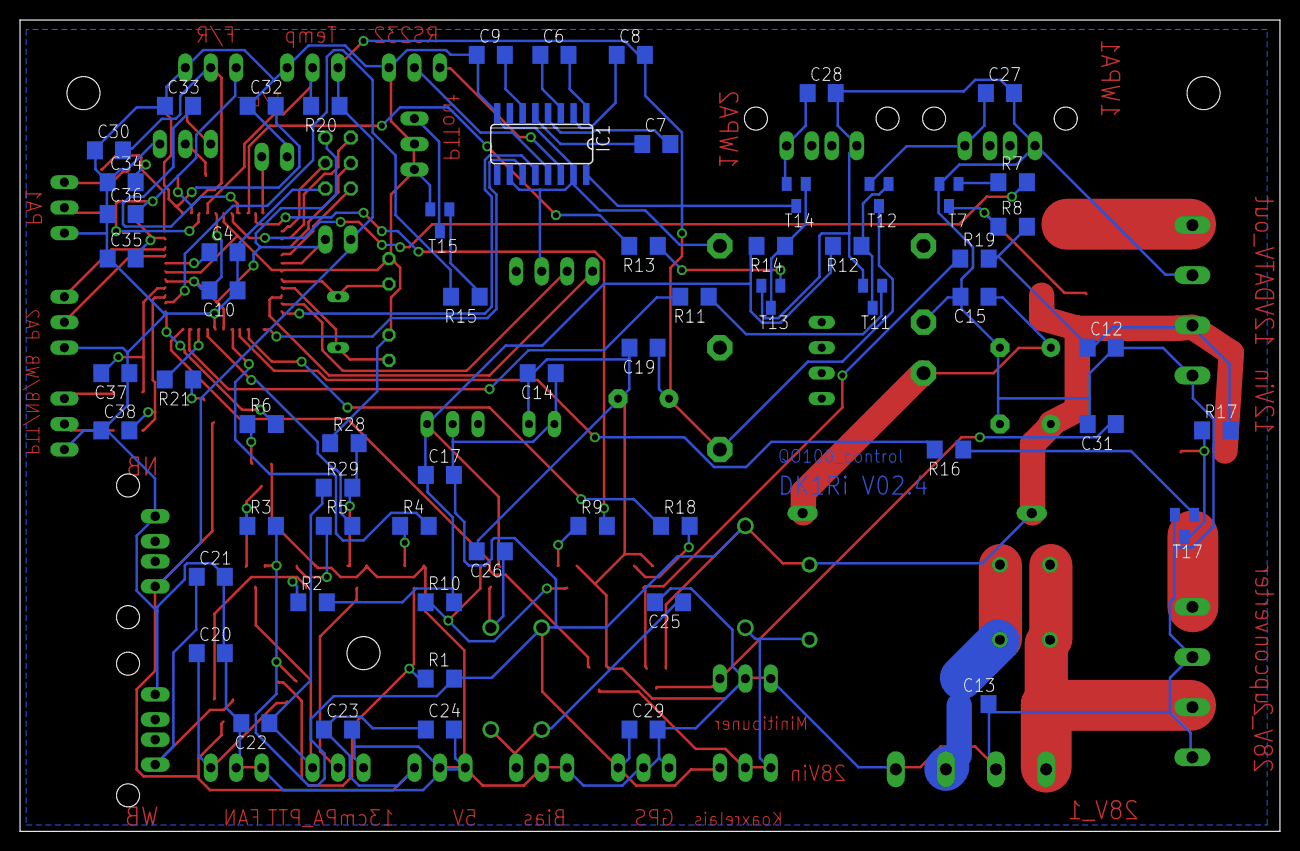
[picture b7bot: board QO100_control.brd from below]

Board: 2 copper layers, 125.7 x 81.0 mm, 132 parts (62 on the bottom side), 91 nets.

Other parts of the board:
U$1, U$2, U$3: 3,3
